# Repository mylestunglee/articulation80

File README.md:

# articulation80

The _articulation80_ keyboard is a split keyboard with 4x9 column splayed keys and 4 thumb keys. The name is inspired from articulated buses, where this keyboard has many connected blocks.

It features:
- Kailh Choc V1 hotswap support with choc spacing
- A detachable inner number row with fixed outer number row
- A detachable numpad
- Serial or I2C connection between halves
- Pro Micro-compatible controller support
- No branding! If you are building this, you may want to add silk-screen to make soldering easier.

I took inspiration from many keyboards:
- The general snappable layout from [Breeze](https://www.afternoonlabs.com/breeze/)
- The pinky stagger from [Kyria](https://blog.splitkb.com/introducing-the-kyria/)
- The column splay and thumb cluster from [Hillside 52](https://github.com/mmccoyd/hillside)
- Many popular keyboards to determine a suitable wiring diagram for TRRS, such as the [Corne](https://github.com/foostan/crkbd)

## Repository Contents

| Name | Description |
|:-|:-|
| `pcb` | KiCad 7 project with symbol diagrams, footprints and 3D models included |
| `layout.FCStd` | FreeCad layout file outlining PCB and plate edges |
| `articulation80` | QMK files for firmware |

`scripts/info_json_matrix`

Generates `info.json` layout data for QMK by running `python generate_layout.py layout.csv`. `layout.csv` maps the visual key position with the pin row and column.

`scripts/verify_geometry`

 Translates points generated by FreeCad into KiCad. `export_points.py` is a script intended to run inside FreeCad to export all points into a text file, called `geometry.txt`. `update_geometry_markers.py` uses `geometry.txt` to aid the correct placement of components on the PCB and edges by placing dummy components as markers. Using the snap tool in KiCad, one can construct the edge by connecting markers. `remove_geometry_markers.py` removes these markers. Perhaps there is a more efficient way to make FreeCad and KiCad work together with existing plugins.

After soldering, copy the `articulation80` sub-directory into `qmk_firmware/keyboards`. Flash with:
```
qmk flash -kb articulation80 -km default -bl dfu-split-left
```
Replace `left` with `right` as necessary. This command assumes the Elite-C has been soldered using I2C. If not, change the bootloader in the command and in the `info.json` file.

## Build Instructions

This build is very similar to existing keyboards. Please refer to the inspired keyboards for full instructions.

### Build Parts

| Name | Count | Remarks |
|:-|:-|:-|
| PCB                   | 2      | |
| Plate                 | 2 | Ensure left and right are cut as required |
| Controller            | 2      | A Pro Micro-compatible controller |
| TRRS jack             | 2      | PJ-320A, ensure pins are through-hole|
| TRRS cable            | 1      | Also called a 4-pin 3.5mm audio auxiliary cable |
| Reset button          | 2      | Optional, PTS526 SM15 SMTR2 LFS recommended|
| Resistors             | 2      | Optional, for I2C connection, RC1206FR-074K7 |
| Diode                 | 80*    | SMD only, 1N4148W-TP, SOD-123 recommended |
| Hot swap key sockets | 80*      | CPG135001S30 |
| Key Switch            | 80*    | |
| Key Cap               | 80*    | Ideally 6 key caps for thumbs |
| Hot swap controller sockets | 4      | Optional, 315-43-112-41-003000 or higher profile.|
| Hot swap pins         | 48     | Optional, 3320-0-00-15-00-00-03-0 |
| Rubber feet           | 12     | Can have more for stability, 6 recommended minimum for each side. SJ-5302 CLEAR recommended. |

*Adjust for number of keys desired.

See the [documentation on QMK](https://github.com/qmk/qmk_firmware/blob/master/docs/feature_split_keyboard.md) for how to solder the resistors. To minimise the complexity of the PCB, the left side controller is soldered upside down. There are four pads which connect the controller to the TRRS jack, these are intended to be soldered on the back side of the keyboard. From left to right with the back side facing up, if using serial connection, solder pads 1 and 4, otherwise if using I2C, solder 2, 3 and 4.

## More Images

Featuring MBK and MCC POM keycaps.

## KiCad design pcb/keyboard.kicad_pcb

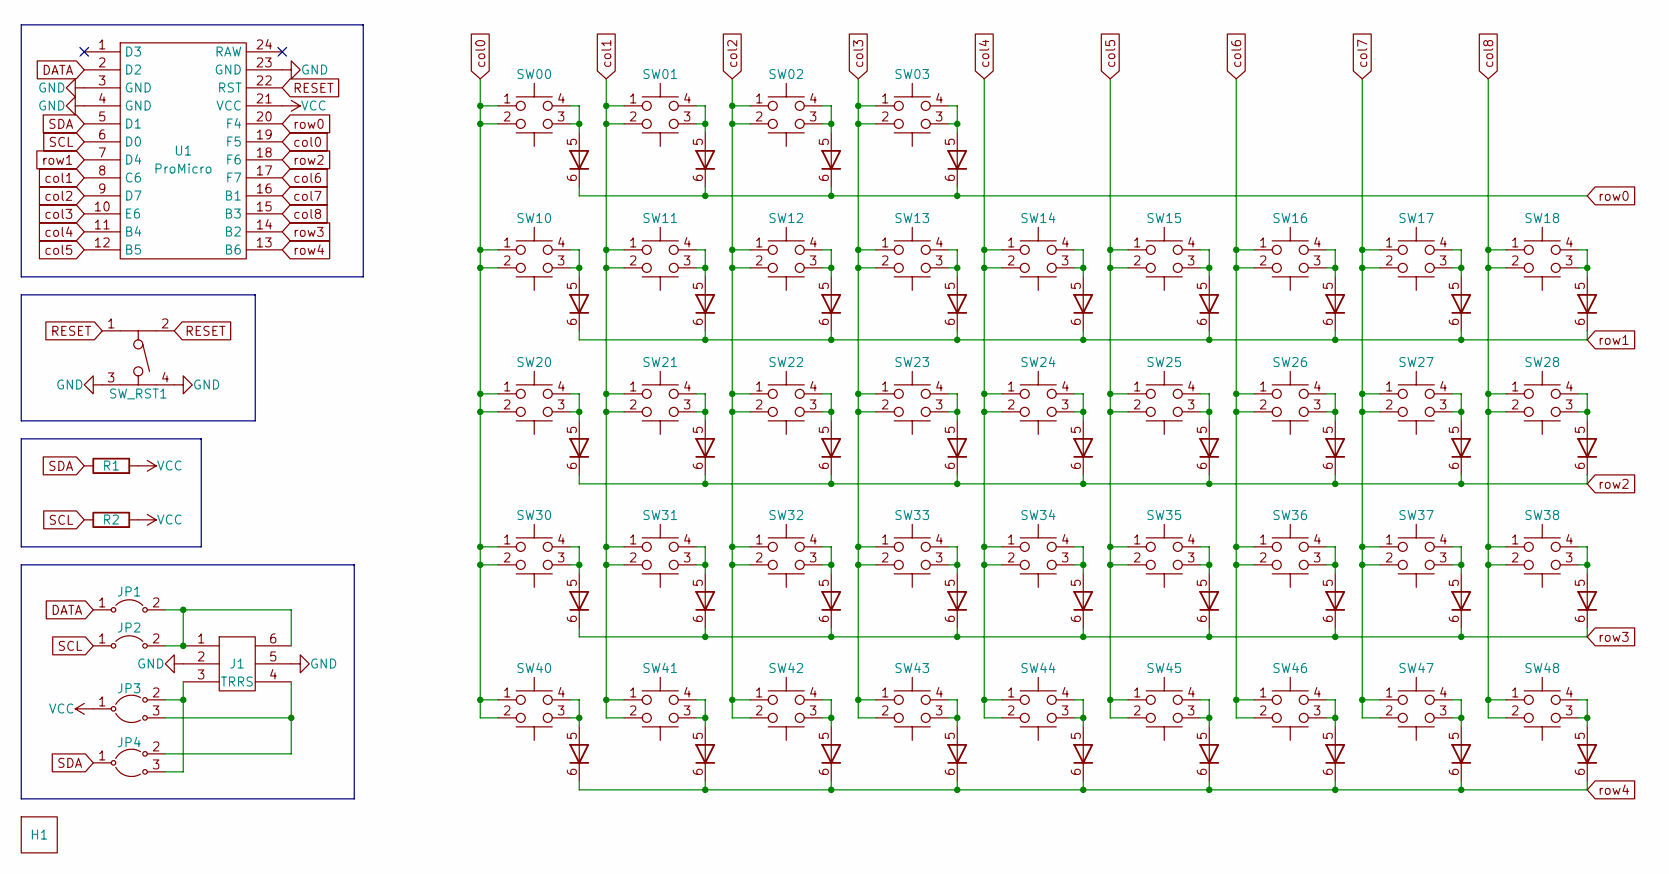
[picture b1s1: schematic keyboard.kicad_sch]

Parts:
H1: RightPlate
J1: TRRS; PJ-320A
JP1, JP2: Jumper
JP3, JP4: JumperSplit
R1, R2: R; SDR18
SW00, SW10, SW14, SW40, SW41: Key; KeyLeft
SW01, SW02, SW11, SW12, SW13, SW16, SW17, SW20, SW21, SW22, SW23, SW24, SW26, SW27, SW30, SW31, SW32, SW33, SW34, SW36, SW37, SW42, SW44, SW46, SW47: Key
SW03, SW15, SW18, SW25, SW28, SW35, SW38, SW43, SW45, SW48: Key; KeyRight
SW_RST1: PTS526; PTS525
U1: ProMicro

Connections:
DATA: JP1.1, U1.2 (D2)
GND: J1.2, J1.5, SW_RST1.3, SW_RST1.4, U1.3 (GND), U1.4 (GND), U1.23 (GND)
unnamed: J1.1, J1.6, JP1.2, JP2.2
unnamed: J1.3, JP3.2, JP4.3
unnamed: J1.4, JP3.3, JP4.2
unnamed: SW00.3, SW00.4, SW00.5
unnamed: SW01.3, SW01.4, SW01.5
unnamed: SW02.3, SW02.4, SW02.5
unnamed: SW03.3, SW03.4, SW03.5
unnamed: SW10.3, SW10.4, SW10.5
unnamed: SW11.3, SW11.4, SW11.5
unnamed: SW12.3, SW12.4, SW12.5
unnamed: SW13.3, SW13.4, SW13.5
unnamed: SW14.3, SW14.4, SW14.5
unnamed: SW15.3, SW15.4, SW15.5
unnamed: SW16.3, SW16.4, SW16.5
unnamed: SW17.3, SW17.4, SW17.5
unnamed: SW18.3, SW18.4, SW18.5
unnamed: SW20.3, SW20.4, SW20.5
unnamed: SW21.3, SW21.4, SW21.5
unnamed: SW22.3, SW22.4, SW22.5
unnamed: SW23.3, SW23.4, SW23.5
unnamed: SW24.3, SW24.4, SW24.5
unnamed: SW25.3, SW25.4, SW25.5
unnamed: SW26.3, SW26.4, SW26.5
unnamed: SW27.3, SW27.4, SW27.5
unnamed: SW28.3, SW28.4, SW28.5
unnamed: SW30.3, SW30.4, SW30.5
unnamed: SW31.3, SW31.4, SW31.5
unnamed: SW32.3, SW32.4, SW32.5
unnamed: SW33.3, SW33.4, SW33.5
unnamed: SW34.3, SW34.4, SW34.5
unnamed: SW35.3, SW35.4, SW35.5
unnamed: SW36.3, SW36.4, SW36.5
unnamed: SW37.3, SW37.4, SW37.5
unnamed: SW38.3, SW38.4, SW38.5
unnamed: SW40.3, SW40.4, SW40.5
unnamed: SW41.3, SW41.4, SW41.5
unnamed: SW42.3, SW42.4, SW42.5
unnamed: SW43.3, SW43.4, SW43.5
unnamed: SW44.3, SW44.4, SW44.5
unnamed: SW45.3, SW45.4, SW45.5
unnamed: SW46.3, SW46.4, SW46.5
unnamed: SW47.3, SW47.4, SW47.5
unnamed: SW48.3, SW48.4, SW48.5
RESET: SW_RST1.1, SW_RST1.2, U1.22 (RST)
SCL: JP2.1, R2.1, U1.6 (D0)
SDA: JP4.1, R1.1, U1.5 (D1)
VCC: JP3.1, R1.2, R2.2, U1.21 (VCC)
col0: SW00.1, SW00.2, SW10.1, SW10.2, SW20.1, SW20.2, SW30.1, SW30.2, SW40.1, SW40.2, U1.19 (F5)
col1: SW01.1, SW01.2, SW11.1, SW11.2, SW21.1, SW21.2, SW31.1, SW31.2, SW41.1, SW41.2, U1.8 (C6)
col2: SW02.1, SW02.2, SW12.1, SW12.2, SW22.1, SW22.2, SW32.1, SW32.2, SW42.1, SW42.2, U1.9 (D7)
col3: SW03.1, SW03.2, SW13.1, SW13.2, SW23.1, SW23.2, SW33.1, SW33.2, SW43.1, SW43.2, U1.10 (E6)
col4: SW14.1, SW14.2, SW24.1, SW24.2, SW34.1, SW34.2, SW44.1, SW44.2, U1.11 (B4)
col5: SW15.1, SW15.2, SW25.1, SW25.2, SW35.1, SW35.2, SW45.1, SW45.2, U1.12 (B5)
col6: SW16.1, SW16.2, SW26.1, SW26.2, SW36.1, SW36.2, SW46.1, SW46.2, U1.17 (F7)
col7: SW17.1, SW17.2, SW27.1, SW27.2, SW37.1, SW37.2, SW47.1, SW47.2, U1.16 (B1)
col8: SW18.1, SW18.2, SW28.1, SW28.2, SW38.1, SW38.2, SW48.1, SW48.2, U1.15 (B3)
row0: SW00.6, SW01.6, SW02.6, SW03.6, U1.20 (F4)
row1: SW10.6, SW11.6, SW12.6, SW13.6, SW14.6, SW15.6, SW16.6, SW17.6, SW18.6, U1.7 (D4)
row2: SW20.6, SW21.6, SW22.6, SW23.6, SW24.6, SW25.6, SW26.6, SW27.6, SW28.6, U1.18 (F6)
row3: SW30.6, SW31.6, SW32.6, SW33.6, SW34.6, SW35.6, SW36.6, SW37.6, SW38.6, U1.14 (B2)
row4: SW40.6, SW41.6, SW42.6, SW43.6, SW44.6, SW45.6, SW46.6, SW47.6, SW48.6, U1.13 (B6)

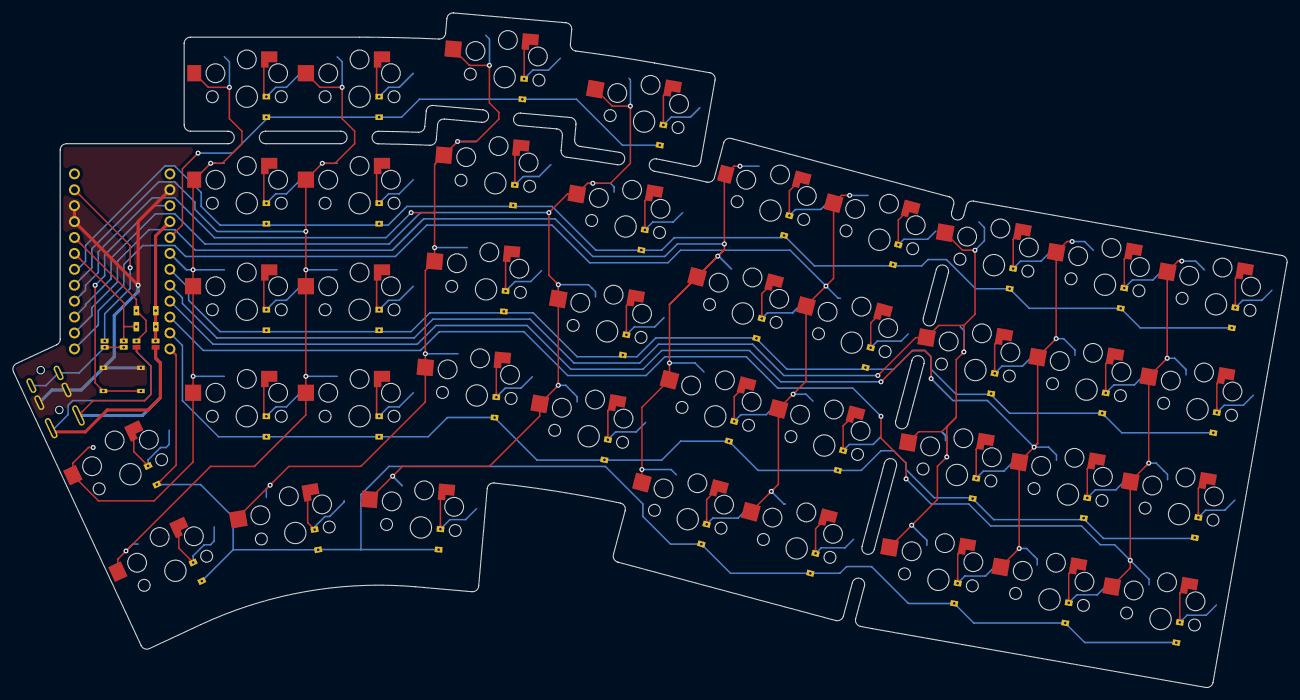
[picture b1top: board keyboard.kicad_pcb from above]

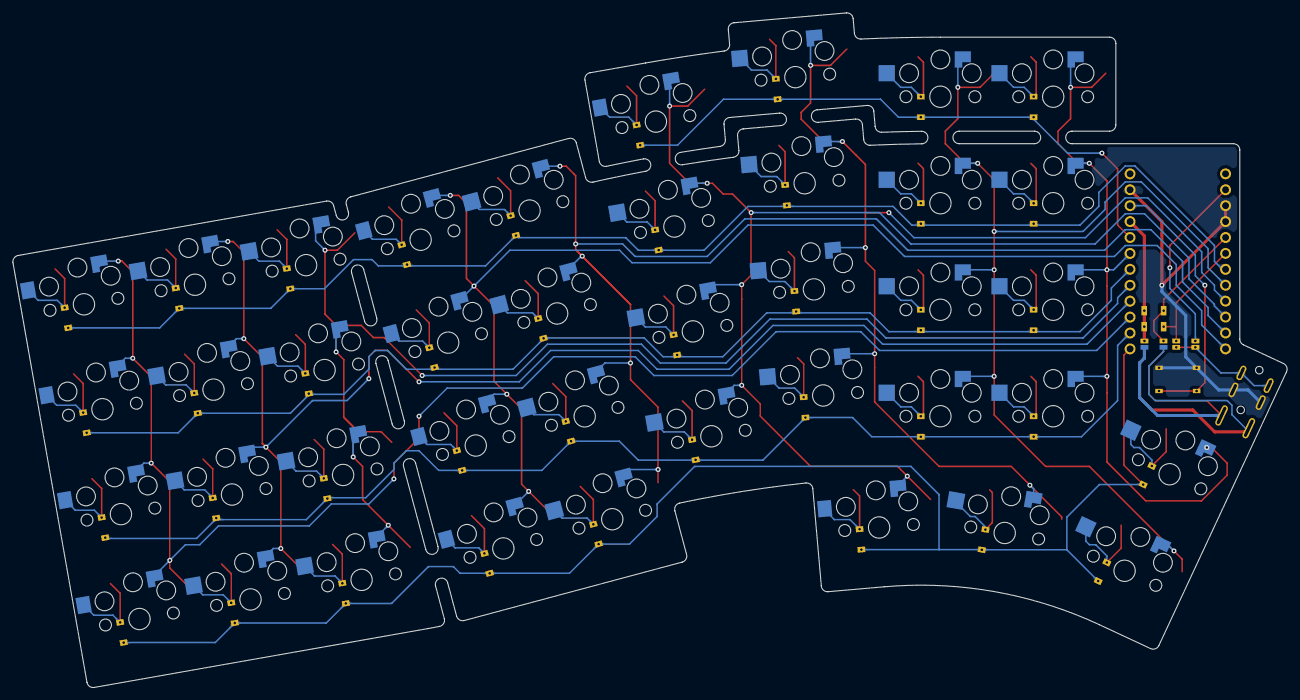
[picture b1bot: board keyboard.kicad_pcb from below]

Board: 2 copper layers, 203.4 x 107.7 mm, 50 parts (3 on the bottom side), 63 nets.

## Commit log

2023-06-12 init
2023-06-19 added new jumpers
2023-06-19 rotate keyboard
2023-06-20 move footprints
2023-06-20 everything but pads in position
2023-06-20 add plates
2023-06-20 move diodes
2023-06-21 add 3d model for plate for main pcb
2023-06-21 rearrange TRRS jack
2023-06-21 reorder jumpers
2023-06-22 start adding traces
2023-06-24 add lots of traces
2023-06-26 setup wiring around promicro
2023-06-26 draft wiring
2023-06-26 tidy wiring
2023-06-27 add fill zones
2023-06-27 redo zones
2023-06-27 move origin
2023-06-29 remove OLED
2023-06-30 complete draft tracing
2023-07-01 adjust pad size for key; reroute with new pads
2023-07-02 add reset button 3d model and trim 1m off TRRS jack front
2023-07-03 move switch layout outside of repo
2023-07-03 rename files
2023-07-03 adjust plates and pcb; remove reset button
2023-07-03 add symbol and footprint for new thin reset button
2023-07-03 update plates
2023-07-03 reroute with new layout; use less vias in each switch
2023-07-04 add layout files
2023-07-04 remove two thumb keys
2023-07-04 remove area under palm
2023-07-04 improve traces
2023-07-05 fix more traces
2023-07-05 improve more traces
2023-07-05 curve a few edges
2023-07-06 remove rounded pro micro pin and widen TRRS traces
2023-07-06 update reset button
    - move 3d model into directory
    - update PTS525 to PTS526
    - centre align reset button with pro micro
2023-07-06 add left plate
2023-07-06 export gerber
2023-07-06 do not have vias on pads
2023-07-07 make reset button double sided and remove silk screen
2023-07-07 correct PTS526 pad sizes
2023-07-07 optimise layout
2023-07-07 add mask for drill holes
2023-07-09 reroute TRRS
2023-07-09 add teardrops
2023-07-09 correct TRRS footprint
2023-07-10 make resistor footprint double sided
2023-07-31 remove unused file
2023-08-26 use offical KiCad gitignore
2023-09-11 add qmk files
2023-09-12 replace circle in arcs, generate images
2023-09-13 move pcb files into pcb directory
2023-09-13 add readme and scripts
2023-09-13 add missing ingredient
2023-09-13 add more photos
2023-09-22 move text to user drawing layer
2023-09-22 ignore pcb export zip
2023-10-08 fix right plate name
